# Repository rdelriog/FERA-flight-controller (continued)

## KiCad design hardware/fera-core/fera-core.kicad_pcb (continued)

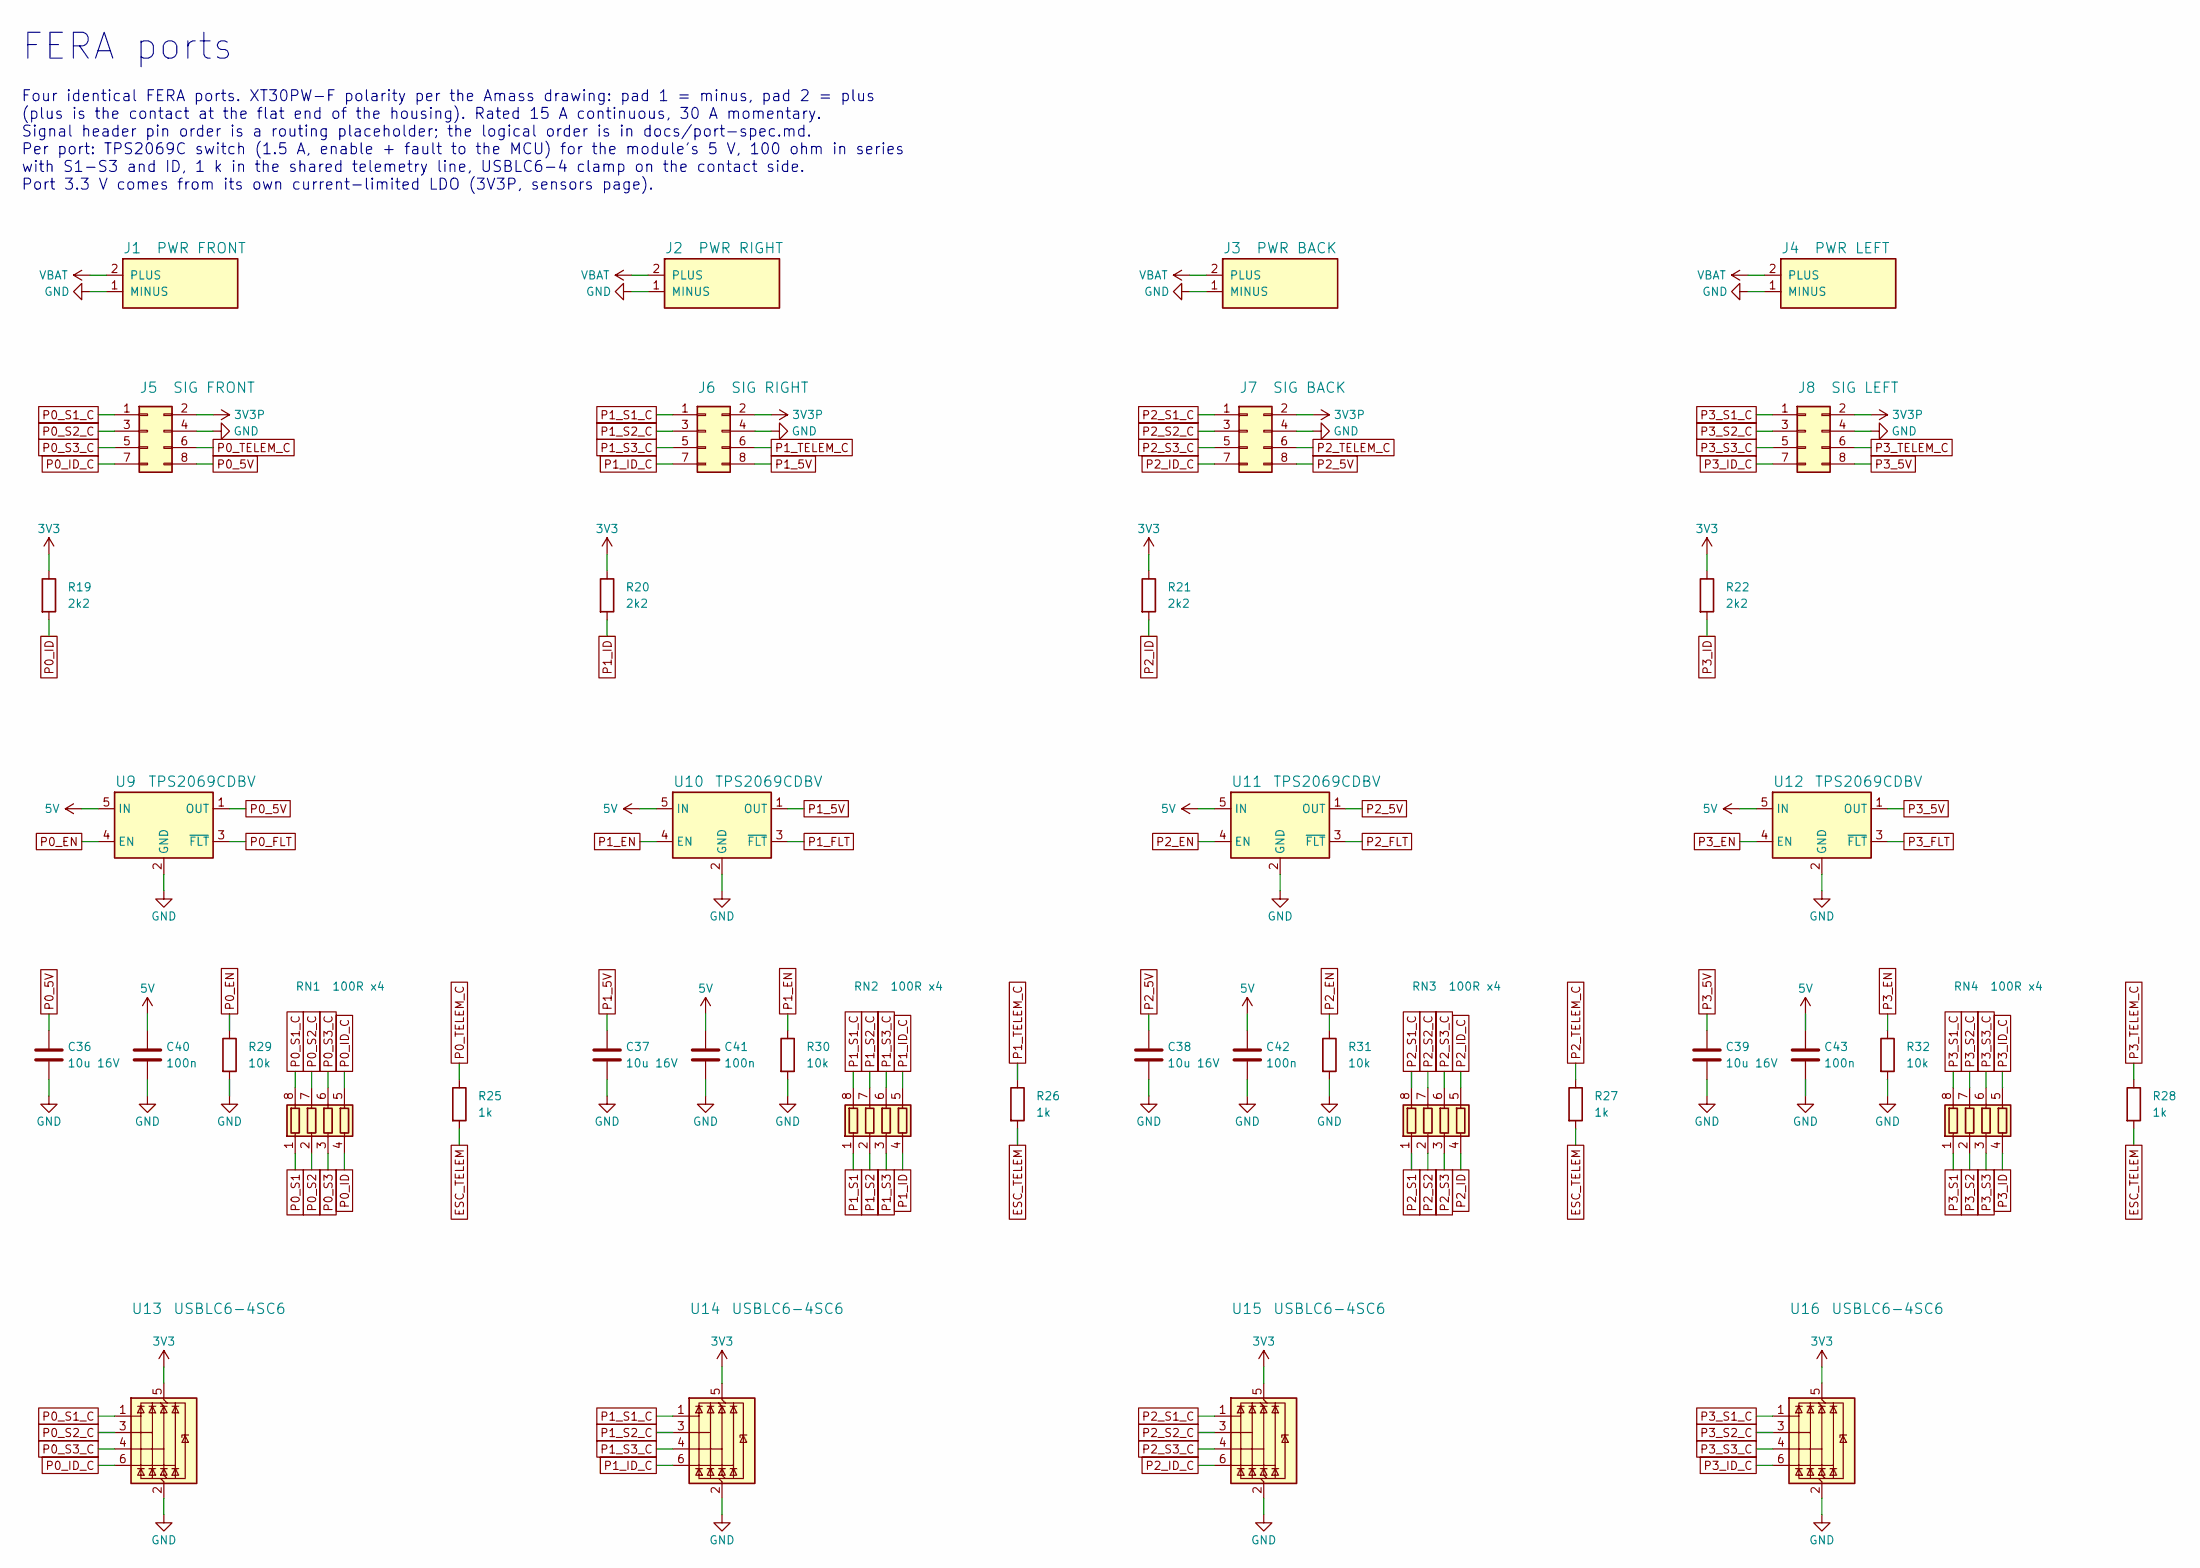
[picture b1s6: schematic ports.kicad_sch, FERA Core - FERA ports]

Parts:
C36, C37, C38, C39: 10u 16V; C_0805_2012Metric
C40, C41, C42, C43: 100n; C_0402_1005Metric
J1: PWR FRONT; AMASS_XT30PW-F_1x02_P2.50mm_Horizontal
J2: PWR RIGHT; AMASS_XT30PW-F_1x02_P2.50mm_Horizontal
J3: PWR BACK; AMASS_XT30PW-F_1x02_P2.50mm_Horizontal
J4: PWR LEFT; AMASS_XT30PW-F_1x02_P2.50mm_Horizontal
J5: SIG FRONT; PinHeader_2x04_P1.27mm_Horizontal
J6: SIG RIGHT; PinHeader_2x04_P1.27mm_Horizontal
J7: SIG BACK; PinHeader_2x04_P1.27mm_Horizontal
J8: SIG LEFT; PinHeader_2x04_P1.27mm_Horizontal
R19, R20, R21, R22: 2k2; R_0402_1005Metric
R25, R26, R27, R28: 1k; R_0402_1005Metric
R29, R30, R31, R32: 10k; R_0402_1005Metric
RN1, RN2, RN3, RN4: 100R x4; R_Array_Convex_4x0402
U9, U10, U11, U12: TPS2069CDBV; SOT-23-5
U13, U14, U15, U16: USBLC6-4SC6; SOT-23-6

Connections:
3V3: R19.1, R20.1, R21.1, R22.1, U13.5 (VBUS), U14.5 (VBUS), U15.5 (VBUS), U16.5 (VBUS); also elsewhere on the board
3V3P: J5.2, J6.2, J7.2, J8.2; also elsewhere on the board
5V: C40.1, C41.1, C42.1, C43.1, U9.5 (IN), U10.5 (IN), U11.5 (IN), U12.5 (IN); also elsewhere on the board
ESC_TELEM: R25.2, R26.2, R27.2, R28.2; also elsewhere on the board
GND: C36.2, C37.2, C38.2, C39.2, C40.2, C41.2, C42.2, C43.2, J1.1 (MINUS), J2.1 (MINUS), J3.1 (MINUS), J4.1 (MINUS), J5.4, J6.4, J7.4, J8.4, R29.2, R30.2, R31.2, R32.2, U9.2 (GND), U10.2 (GND), U11.2 (GND), U12.2 (GND), U13.2 (GND), U14.2 (GND), U15.2 (GND), U16.2 (GND); also elsewhere on the board
P0_5V: C36.1, J5.8, U9.1 (OUT)
P0_EN: R29.1, U9.4 (EN); also elsewhere on the board
P0_FLT: U9.3 (~FLT); also elsewhere on the board
P0_ID: R19.2, RN1.4 (R4.1); also elsewhere on the board
P0_ID_C: J5.7, RN1.5 (R4.2), U13.6 (I/O4)
P0_S1: RN1.1 (R1.1); also elsewhere on the board
P0_S1_C: J5.1, RN1.8 (R1.2), U13.1 (I/O1)
P0_S2: RN1.2 (R2.1); also elsewhere on the board
P0_S2_C: J5.3, RN1.7 (R2.2), U13.3 (I/O2)
P0_S3: RN1.3 (R3.1); also elsewhere on the board
P0_S3_C: J5.5, RN1.6 (R3.2), U13.4 (I/O3)
P0_TELEM_C: J5.6, R25.1
P1_5V: C37.1, J6.8, U10.1 (OUT)
P1_EN: R30.1, U10.4 (EN); also elsewhere on the board
P1_FLT: U10.3 (~FLT); also elsewhere on the board
P1_ID: R20.2, RN2.4 (R4.1); also elsewhere on the board
P1_ID_C: J6.7, RN2.5 (R4.2), U14.6 (I/O4)
P1_S1: RN2.1 (R1.1); also elsewhere on the board
P1_S1_C: J6.1, RN2.8 (R1.2), U14.1 (I/O1)
P1_S2: RN2.2 (R2.1); also elsewhere on the board
P1_S2_C: J6.3, RN2.7 (R2.2), U14.3 (I/O2)
P1_S3: RN2.3 (R3.1); also elsewhere on the board
P1_S3_C: J6.5, RN2.6 (R3.2), U14.4 (I/O3)
P1_TELEM_C: J6.6, R26.1
P2_5V: C38.1, J7.8, U11.1 (OUT)
P2_EN: R31.1, U11.4 (EN); also elsewhere on the board
P2_FLT: U11.3 (~FLT); also elsewhere on the board
P2_ID: R21.2, RN3.4 (R4.1); also elsewhere on the board
P2_ID_C: J7.7, RN3.5 (R4.2), U15.6 (I/O4)
P2_S1: RN3.1 (R1.1); also elsewhere on the board
P2_S1_C: J7.1, RN3.8 (R1.2), U15.1 (I/O1)
P2_S2: RN3.2 (R2.1); also elsewhere on the board
P2_S2_C: J7.3, RN3.7 (R2.2), U15.3 (I/O2)
P2_S3: RN3.3 (R3.1); also elsewhere on the board
P2_S3_C: J7.5, RN3.6 (R3.2), U15.4 (I/O3)
P2_TELEM_C: J7.6, R27.1
P3_5V: C39.1, J8.8, U12.1 (OUT)
P3_EN: R32.1, U12.4 (EN); also elsewhere on the board
P3_FLT: U12.3 (~FLT); also elsewhere on the board
P3_ID: R22.2, RN4.4 (R4.1); also elsewhere on the board
P3_ID_C: J8.7, RN4.5 (R4.2), U16.6 (I/O4)
P3_S1: RN4.1 (R1.1); also elsewhere on the board
P3_S1_C: J8.1, RN4.8 (R1.2), U16.1 (I/O1)
P3_S2: RN4.2 (R2.1); also elsewhere on the board
P3_S2_C: J8.3, RN4.7 (R2.2), U16.3 (I/O2)
P3_S3: RN4.3 (R3.1); also elsewhere on the board
P3_S3_C: J8.5, RN4.6 (R3.2), U16.4 (I/O3)
P3_TELEM_C: J8.6, R28.1
VBAT: J1.2 (PLUS), J2.2 (PLUS), J3.2 (PLUS), J4.2 (PLUS); also elsewhere on the board

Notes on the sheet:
FERA ports
Four identical FERA ports. XT30PW-F polarity per the Amass drawing: pad 1 = minus, pad 2 = plus (plus is the contact at the flat end of the housing). Rated 15 A continuous, 30 A momentary. Signal header pin order is a routing placeholder; the logical order is in docs/port-spec.md. Per port: TPS2069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

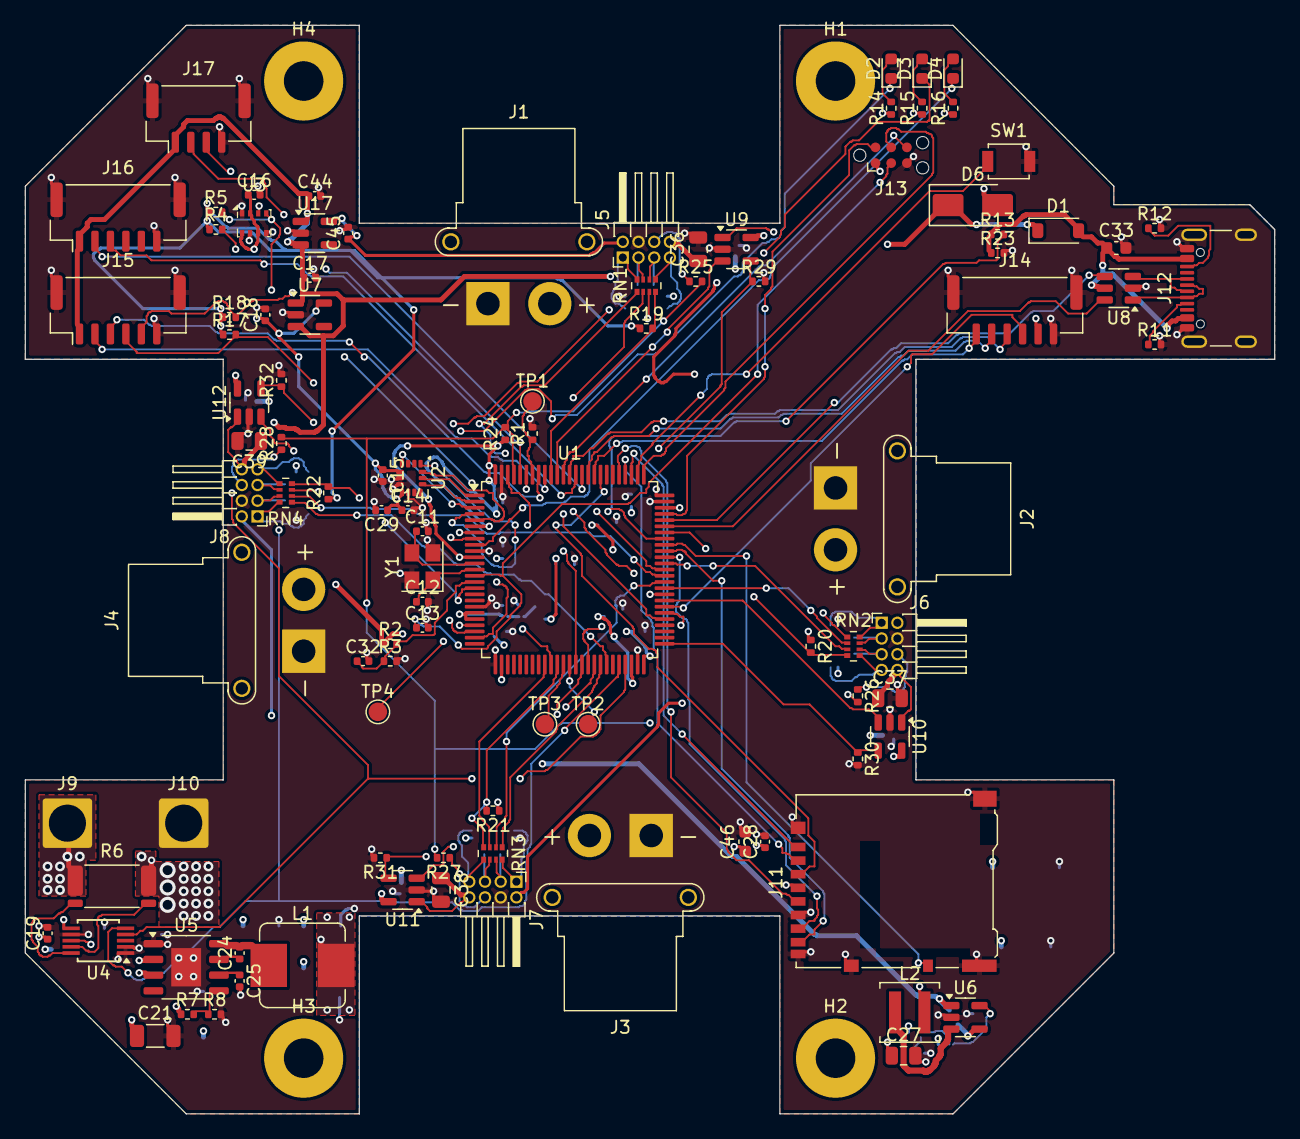
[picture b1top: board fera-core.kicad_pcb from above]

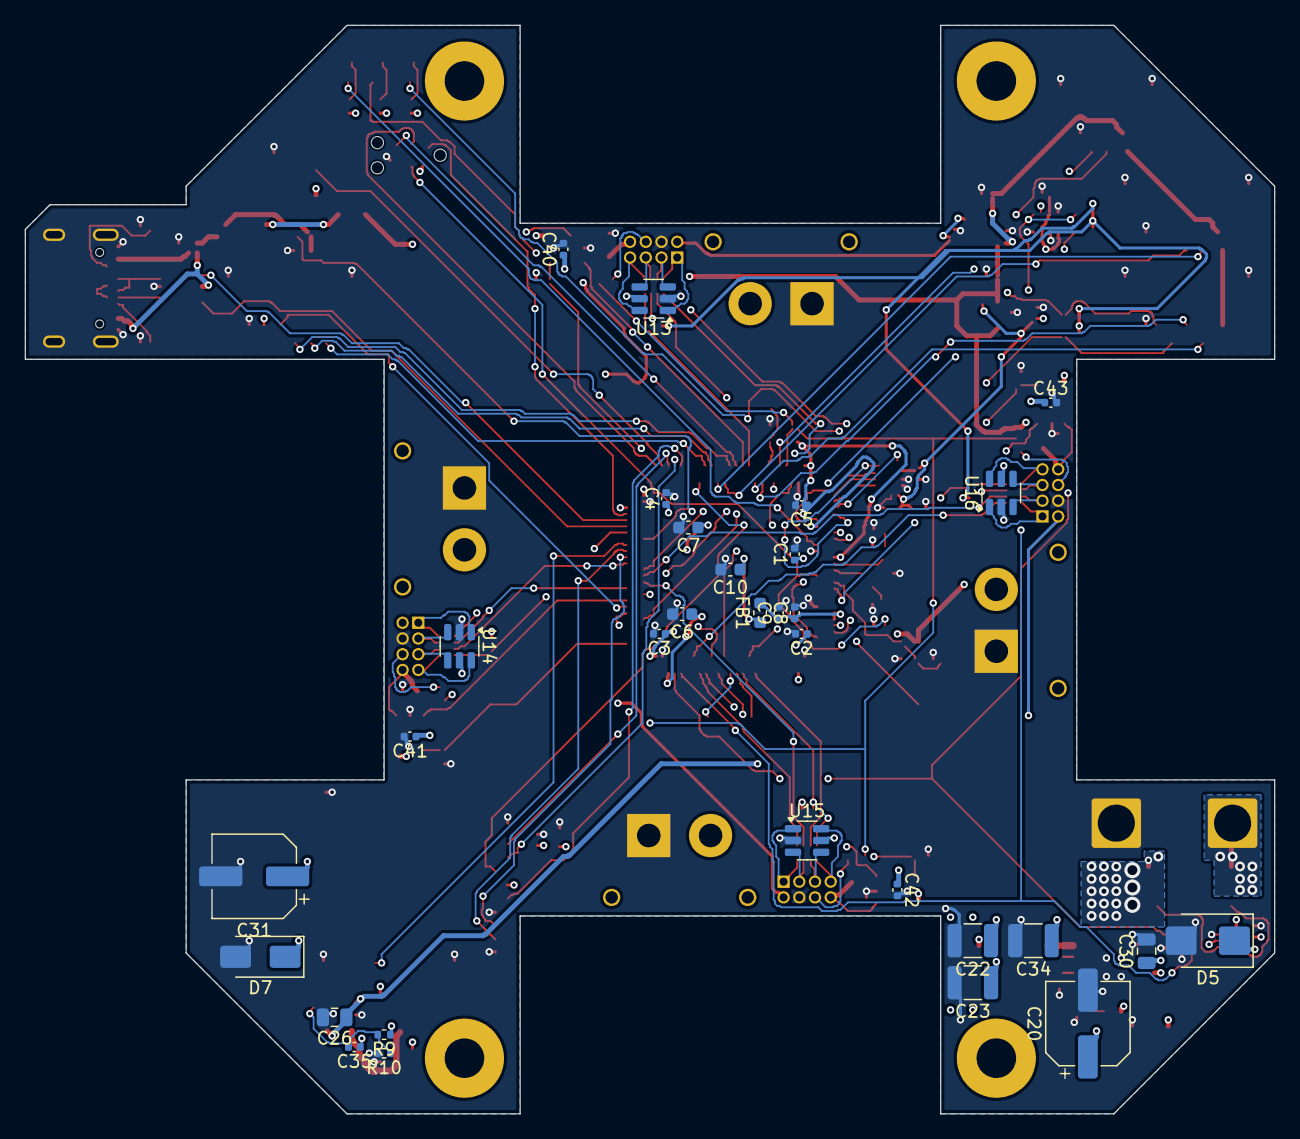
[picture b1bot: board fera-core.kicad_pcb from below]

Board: 6 copper layers, 101.0 x 88.0 mm, 136 parts (31 on the bottom side), 120 nets.

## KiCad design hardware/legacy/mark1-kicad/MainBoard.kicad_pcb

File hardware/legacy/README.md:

# Legacy hardware (reference only)

| Folder | What | Why it is not carried forward |
|---|---|---|
| `mark1-kicad/` | KiCad 8 "Mark I" main board: STM32F730R8, MPU-9250, BMP280, 4x JST-XH arm ports. `GND_VLIPO_Plane.kicad_pcb` is the newest layout. | 64 KB flash cannot run PX4; VDD pins tied to the VBAT net, VCAP/NRST/SWD unconnected, no crystal, no USB-C CC resistors, no SD card, no battery sensing; arm port has one signal and 3 A pins. |
| `altium-2021/` | Altium dev board from 2021: STM32F103, MPU-6050, BMP280, microSD. | Altium format, obsolete parts. |
| `cubemx-nucleo-f722/` | STM32CubeMX project for a Nucleo-F722ZE (template only, empty main loop). | PX4 replaces the HAL-based firmware. |
| `mechanical/` | Hub baseplate DXF/DWG from the first prototype. | Re-authored parametrically in `cad/`. |

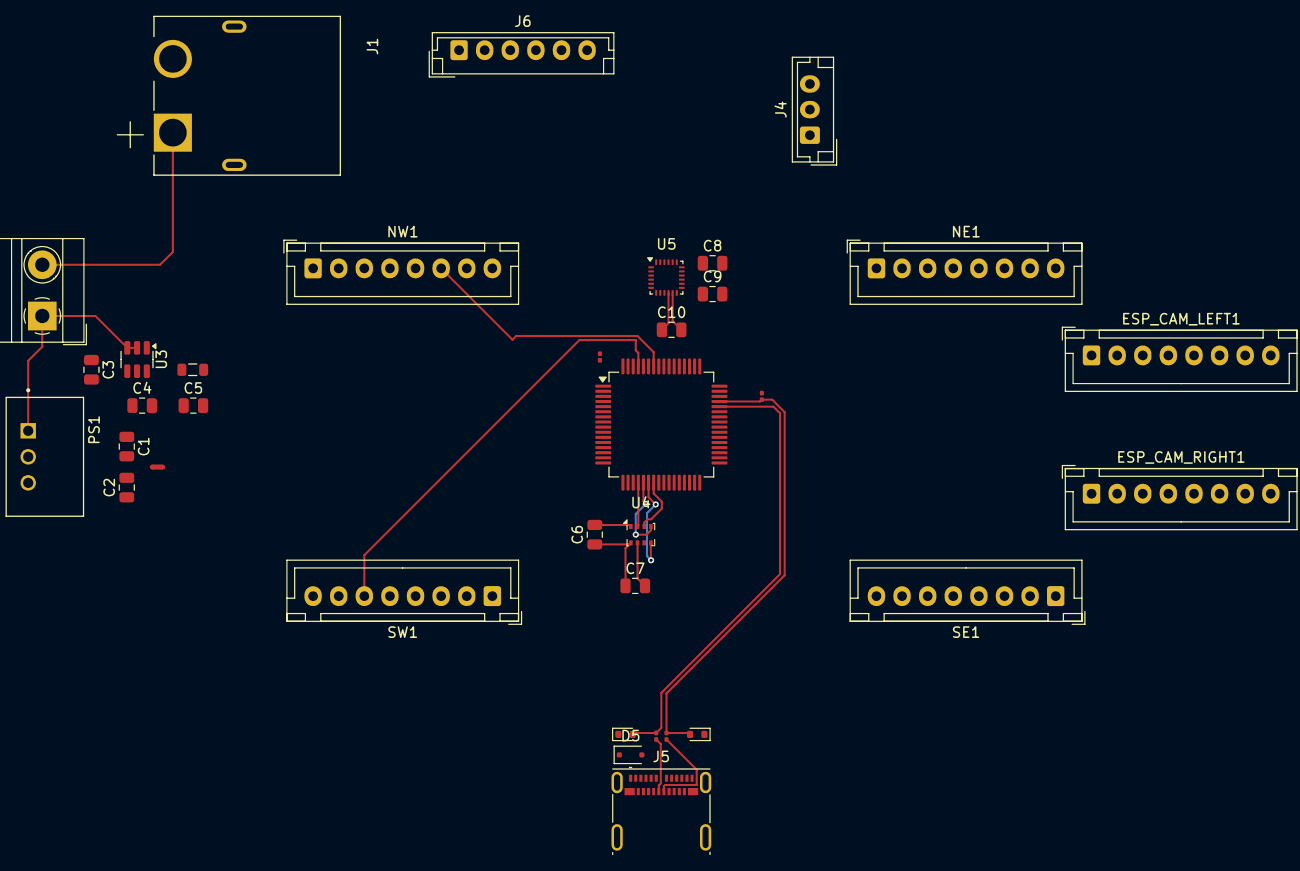
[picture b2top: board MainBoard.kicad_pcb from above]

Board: 2 copper layers, 35 parts (0 on the bottom side), 28 nets.

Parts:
C1, C3: 10u; C_0805_2012Metric
C2, C4, C5, C6, C7: 22u; C_0805_2012Metric
C8: 10n; C_0805_2012Metric
C9, C10: 0.1u; C_0805_2012Metric
D1, D2: ESD5Zxx; D_SOD-523
D5: BAT54J; D_SOD-323F
ESP_CAM_LEFT1: Conn_01x08_Socket; JST_XH_B8B-XH-A_1x08_P2.50mm_Vertical
ESP_CAM_RIGHT1: Conn_01x08_Socket; JST_XH_B8B-XH-A_1x08_P2.50mm_Vertical
J1: XT60PW-M; AMASS_XT60PW-M
J3: Screw_Terminal_01x02; TerminalBlock_MetzConnect_Type011_RT05502HBWC_1x02_P5.00mm_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
J4: Conn_01x03_Pin; JST_EH_B3B-EH-A_1x03_P2.50mm_Vertical
J5: USB_C_Receptacle; USB_C_Receptacle_Molex_105450-0101
J6: Conn_01x06_Socket; JST_EH_B6B-EH-A_1x06_P2.50mm_Vertical
L1: L; L_0805_2012Metric
NE1: Conn_01x08_Socket; JST_XH_B8B-XH-A_1x08_P2.50mm_Vertical
NT2: NetTie_2; NetTie-2_SMD_Pad0.5mm
NW1: Conn_01x08_Socket; JST_XH_B8B-XH-A_1x08_P2.50mm_Vertical
PS1: K7803-500R3; CONV_K7803-500R3
R1: 10k; R_0201_0603Metric
R2, R3: 22/33; R_0201_0603Metric
R7: 1.5k; R_0201_0603Metric
SE1: Conn_01x08_Socket; JST_XH_B8B-XH-A_1x08_P2.50mm_Vertical
SW1: Conn_01x08_Socket; JST_XH_B8B-XH-A_1x08_P2.50mm_Vertical
U1: STM32F730R8Tx; LQFP-64_10x10mm_P0.5mm
U3: AP63205WU; TSOT-23-6
U4: BMP280; Bosch_LGA-8_2x2.5mm_P0.65mm_ClockwisePinNumbering
U5: MPU-9250; InvenSense_QFN-24_3x3mm_P0.4mm

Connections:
/3V3: C2.1, C6.1, C7.1, C8.2, C9.2, ESP_CAM_RIGHT1.1, PS1.3 (+VO), R7.1, U4.6 (VDDIO), U4.8 (VDD), U5.8 (VDDIO), U5.13 (VDD)
/5V0: C5.1, D5.1 (K), J4.1, J6.1, L1.2, U3.1 (FB)
/GPS_RX: J6.2, U1.43 (PA10)
/GPS_TX: J6.3, U1.42 (PA9)
/MPU_SCL: U1.28 (PB10), U5.23 (SCL/SCLK)
/MPU_SDA: U1.29 (PB11), U5.24 (SDA/MOSI)
/PRESS_CSB: U1.20 (PA4), U4.2 (CSB)
/PRESS_SCK: U1.21 (PA5), U4.4 (SCK)
/PRESS_SD0: U1.22 (PA6), U4.5 (SDO)
/PRESS_SD1: U1.23 (PA7), U4.3 (SDI)
/SGN_NE: NE1.6, U1.59 (PB7)
/SGN_NW: NW1.6, U1.58 (PB6)
/SGN_SE: SE1.6, U1.62 (PB9)
/SGN_SW: SW1.6, U1.61 (PB8)
/USB_D_Conn_N: J5.B7 (D-), R2.2
/USB_D_Conn_P: J5.B6 (D+), R3.2
/USB_D_N: D2.2 (A), R2.1, U1.44 (PA11)
/USB_D_P: D1.2 (A), R3.1, R7.2, U1.45 (PA12)
/V_LIPO: C1.1, C3.1, J3.1, NE1.3, NE1.4, NE1.5, NW1.3, NW1.4, NW1.5, PS1.1 (VIN), SE1.3, SE1.4, SE1.5, SW1.3, SW1.4, SW1.5, U3.2 (EN), U3.3 (IN)
/V_LIPO_BEFORE_SW: J1.1 (+), J3.2
GND: C1.2, C2.2, C3.2, C5.2, C6.2, C7.2, C8.1, C9.1, C10.2, D1.1 (K), D2.1 (K), ESP_CAM_LEFT1.2, ESP_CAM_RIGHT1.4, J4.3, J5.A1 (GND), J5.A12 (GND), J5.B1 (GND), J5.B12 (GND), J6.6, NE1.7, NE1.8, NT2.1, NW1.7, NW1.8, PS1.2 (GND), R1.1, SE1.7, SE1.8, SW1.7, SW1.8, U1.12 (VSSA), U1.18 (VSS), U1.31 (VSS), U1.47 (VSS), U1.63 (VSS), U3.4 (GND), U4.1 (GND), U4.7 (GND), U5.11 (FSYNC), U5.18 (GND)
unnamed: D5.2 (A), J5.A4 (VBUS), J5.A9 (VBUS), J5.B4 (VBUS), J5.B9 (VBUS)
unnamed: R1.2, U1.60 (BOOT0)
unnamed: U1.1 (VBAT), U1.13 (VDDA), U1.19 (VDD), U1.32 (VDD), U1.48 (VDD), U1.64 (VDD)
unnamed: C4.2, U3.6 (BST)
unnamed: C4.1, L1.1, U3.5 (SW)
unnamed: C10.1, U5.10 (REGOUT)
PWR_GND: J1.2 (-), NE1.1, NE1.2, NT2.2, NW1.1, NW1.2, SE1.1, SE1.2, SW1.1, SW1.2

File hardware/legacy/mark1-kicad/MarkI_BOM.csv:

Reference,Value,Datasheet,Footprint,Qty,DNP
"C1,C3",10u,~,Capacitor_SMD:C_0805_2012Metric,2,
"C2,C4,C5,C6,C7",22u,~,Capacitor_SMD:C_0805_2012Metric,5,
C8,10n,~,Capacitor_SMD:C_0805_2012Metric,1,
"C9,C10",0.1u,~,Capacitor_SMD:C_0805_2012Metric,2,
"D1,D2",ESD5Zxx,https://www.onsemi.com/pdf/datasheet/esd5z2.5t1-d.pdf,Diode_SMD:D_SOD-523,2,
D5,BAT54J,https://assets.nexperia.com/documents/data-sheet/BAT54J.pdf,Diode_SMD:D_SOD-323F,1,
J1,XT60PW-M,,XT60PW-M:AMASS_XT60PW-M,1,
J2,Conn_01x04_Socket,~,Connector_JST:JST_XH_B4B-XH-AM_1x04_P2.50mm_Vertical,1,
J3,Screw_Terminal_01x02,~,TerminalBlock_MetzConnect:TerminalBlock_MetzConnect_Type011_RT05502HBWC_1x02_P5.00mm_Horizontal,1,
J4,Conn_01x03_Pin,~,Connector_JST:JST_EH_B3B-EH-A_1x03_P2.50mm_Vertical,1,
J5,USB_C_Receptacle,https://www.usb.org/sites/default/files/documents/usb_type-c.zip,Connector_USB:USB_C_Receptacle_Molex_105450-0101,1,
J6,Conn_01x06_Socket,~,Connector_JST:JST_EH_B6B-EH-A_1x06_P2.50mm_Vertical,1,
L1,L,~,Inductor_SMD:L_0805_2012Metric,1,
"NE1,NW1,SE1,SW1",Conn_01x08_Socket,~,Connector_JST:JST_XH_B8B-XH-A_1x08_P2.50mm_Vertical,4,
PS1,K7803-500R3,,K7803-500R3:CONV_K7803-500R3,1,
R1,10k,~,Resistor_SMD:R_0201_0603Metric,1,
"R2,R3",22/33,~,Resistor_SMD:R_0201_0603Metric,2,
R7,1.5k,~,Resistor_SMD:R_0201_0603Metric,1,
SW2,SW_Push,~,Button_Switch_THT:SW_PUSH_6mm,1,
U1,STM32F730R8Tx,https://www.st.com/resource/en/datasheet/stm32f730r8.pdf,Package_QFP:LQFP-64_10x10mm_P0.5mm,1,
U3,AP63205WU,https://www.diodes.com/assets/Datasheets/AP63200-AP63201-AP6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,Package_TO_SOT_SMD:TSOT-23-6,1,
U4,BMP280,https://ae-bst.resource.bosch.com/media/_tech/media/datashee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,Package_LGA:Bosch_LGA-8_2x2.5mm_P0.65mm_ClockwisePinNumbering,1,
U5,MPU-9250,https://invensense.tdk.com/wp-content/uploads/2015/02/PS-MPU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,Sensor_Motion:InvenSense_QFN-24_3x3mm_P0.4mm,1,

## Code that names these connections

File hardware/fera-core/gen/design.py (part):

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section("mcu", "MCU, clock, debug, status")
MCU_NETS = {
    # port outputs: one timer per role (S1 = TIM1, S2 = TIM4, S3 = TIM3)
    "PE9": "P0_S1", "PE11": "P1_S1", "PE13": "P2_S1", "PE14": "P3_S1",
    "PD12": "P0_S2", "PD13": "P1_S2", "PD14": "P2_S2", "PD15": "P3_S2",
    "PC6": "P0_S3", "PC7": "P1_S3", "PB0": "P2_S3", "PB1": "P3_S3",
    "PB5": "P0_ID", "PA10": "P1_ID", "PB2": "P2_ID", "PC1": "P3_ID",
    "PD3": "LATCH0", "PD4": "LATCH1", "PD7": "LATCH2", "PD10": "LATCH3",
    # port 5 V switches: enable (high = on) and fault (low = overcurrent), each on the MCU
    # edge that faces its port
    "PE1": "P0_EN", "PB12": "P1_EN", "PE12": "P2_EN", "PA2": "P3_EN",
    "PB4": "P0_FLT", "PD11": "P1_FLT", "PE10": "P2_FLT", "PA1": "P3_FLT",
    "PE0": "ESC_TELEM",
    # IMU on SPI4: these five pins are the MCU corner next to the sensor
    "PE2": "IMU_SCK", "PE5": "IMU_MISO", "PE6": "IMU_MOSI", "PE3": "IMU_CS", "PE4": "IMU_DRDY",
    "PB10": "I2C2_SCL", "PB11": "I2C2_SDA",
    # microSD
    "PC8": "SD_D0", "PC9": "SD_D1", "PC10": "SD_D2", "PC11": "SD_D3", "PC12": "SD_CK",
    "PD2": "SD_CMD", "PA8": "SD_DET",
    # connectors
    "PB6": "GPS_TX", "PB7": "GPS_RX", "PB8": "I2C1_SCL", "PB9": "I2C1_SDA",
    "PD5": "TELEM1_TX", "PD6": "TELEM1_RX", "PD8": "RC_TX", "PD9": "RC_RX",
    "PE8": "DBG_TX", "PE7": "DBG_RX",
    "PA11": "USB_D_N", "PA12": "USB_D_P", "PA9": "USB_VBUS_SENSE",
    "PA13": "SWDIO", "PA14": "SWCLK", "PB3": "SWO", "NRST": "NRST",
    # housekeeping
    "PC0": "V5_SENSE", "PA0": "BUZZER", "PC13": "LED_R", "PC14": "LED_G", "PC15": "LED_B",
    "PA15": "SAFETY_BTN", "BOOT0": "BOOT0", "PH0": "OSC_IN", "PH1": "OSC_OUT",
    # power
    "VDD": "3V3", "VSS": "GND", "VDDA": "3V3A", "VREF+": "3V3A", "VSSA": "GND", "VBAT": "3V3",
}
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# The peripheral function each signal relies on; checked against the alternate-function
# list in KiCad's STM32H743VITx symbol by make_schematic.py.
MCU_FUNCS = {
    "PE9": "TIM1_CH1", "PE11": "TIM1_CH2", "PE13": "TIM1_CH3", "PE14": "TIM1_CH4",
    "PD12": "TIM4_CH1", "PD13": "TIM4_CH2", "PD14": "TIM4_CH3", "PD15": "TIM4_CH4",
    "PC6": "TIM3_CH1", "PC7": "TIM3_CH2", "PB0": "TIM3_CH3", "PB1": "TIM3_CH4",
    "PE0": "UART8_RX",
    "PE2": "SPI4_SCK", "PE5": "SPI4_MISO", "PE6": "SPI4_MOSI",
    "PB10": "I2C2_SCL", "PB11": "I2C2_SDA", "PB8": "I2C1_SCL", "PB9": "I2C1_SDA",
    "PC8": "SDMMC1_D0", "PC9": "SDMMC1_D1", "PC10": "SDMMC1_D2", "PC11": "SDMMC1_D3",
    "PC12": "SDMMC1_CK", "PD2": "SDMMC1_CMD",
    "PB6": "USART1_TX", "PB7": "USART1_RX", "PD5": "USART2_TX", "PD6": "USART2_RX",
    "PD8": "USART3_TX", "PD9": "USART3_RX", "PE8": "UART7_TX", "PE7": "UART7_RX",
    "PA11": "USB_OTG_FS_DM", "PA12": "USB_OTG_FS_DP", "PA9": "USB_OTG_FS_VBUS",
    "PA13": "DEBUG_JTMS-SWDIO", "PA14": "DEBUG_JTCK-SWCLK", "PB3": "DEBUG_JTDO-SWO",
    "PC0": "ADC1_INP10", "PA0": "TIM2_CH1", "PH0": "RCC_OSC_IN", "PH1": "RCC_OSC_OUT",
}

part("U1", "Package_QFP:LQFP-100_14x14mm_P0.5mm", "STM32H743VIT6", 0, 0, nets="MCU")
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for i, (name, x) in enumerate((("R", 26.0), ("G", 28.5), ("B", 31.0))):
    part(f"D{i + 2}", "LED_SMD:LED_0603_1608Metric", f"LED {name}", x, -40.5, 90,
         nets={"1": f"LED_{name}", "2": f"LED_{name}_A"}, note="Pad 1 = cathode, sunk by the MCU.")
    # PC13-15 may sink about 3 mA; green and blue need less resistance than red to be visible
    res(f"R{14 + i}", "680R" if name == "R" else "330R", x, -37.3, "3V3", f"LED_{name}_A", rot=90)
section("io", None)
part("J14", GH6, "LATCH", 36.0, -21.0,
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
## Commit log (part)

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2025-10-23 starter commit starter commit
